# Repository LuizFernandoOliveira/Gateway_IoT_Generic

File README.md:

# Gateway IoT Multi-Protocolo (MSP430 version)

## Descrição
Diferentemente das tradicionais SBCs baseadas em MPUs de alta performance, este circuito de Gateway IoT é baseado em um MCU para aplicações que necessitam gerenciar a sua rede IoT no modo ultra-low power.

---

## Descrições técnicas
- Microcontrolador: MSP430FR6005;
- Alimentação externa de 5V;
- Possui a capacidade de realizar a comunicação com até 4 periféricos UARTs padrão FAPLO;
- Capacidade de se comunicar por meio do protocolo de comunicação:
  - 4 x UARTs (UART0, UART1, UART2, UART3);
  - 1 x RS-485 (UART2);
  - 1 x I2C (UART1);
  - 2 x SPIs (UART0 e UART1);
- Possui LEDs de troca de dados da UART0;
- Todos os demais pinos dos conectores padrão FAPLO podem ser usados como pinos de propósito gerais.

---

## Estrutura do repositório
Os arquivos de hardware foram desenvolvidos utilizando o KiCad 9.0.
- **`.kicad_pcb`**: Layout da placa de circuito impresso (Board).
- **`.kicad_sch`**: Esquemático eletrônico do sistema (Schematic).
- **`.kicad_pro`**: Gerenciador de projeto do KiCad (Project).

---

## Autor
**Dr. Luiz Fernando Pinto de Oliveira**

*Engenheiro Eletrônico especializado em Sistemas Embarcados e Ultra-Low Power.*
- **Website:** [FAPLO](https://faplo.webnode.page/)
- **LinkedIn:** [lfpo](https://www.linkedin.com/in/lfpo/)

---

Shield: [![CC BY-NC-ND 4.0][cc-by-nc-nd-shield]][cc-by-nc-nd]

This work is licensed under a
[Creative Commons Attribution-NonCommercial-NoDerivs 4.0 International License][cc-by-nc-nd].

[![CC BY-NC-ND 4.0][cc-by-nc-nd-image]][cc-by-nc-nd]

[cc-by-nc-nd]: http://creativecommons.org/licenses/by-nc-nd/4.0/
[cc-by-nc-nd-image]: https://licensebuttons.net/l/by-nc-nd/4.0/88x31.png
[cc-by-nc-nd-shield]: https://img.shields.io/badge/License-CC%20BY--NC--ND%204.0-lightgrey.svg

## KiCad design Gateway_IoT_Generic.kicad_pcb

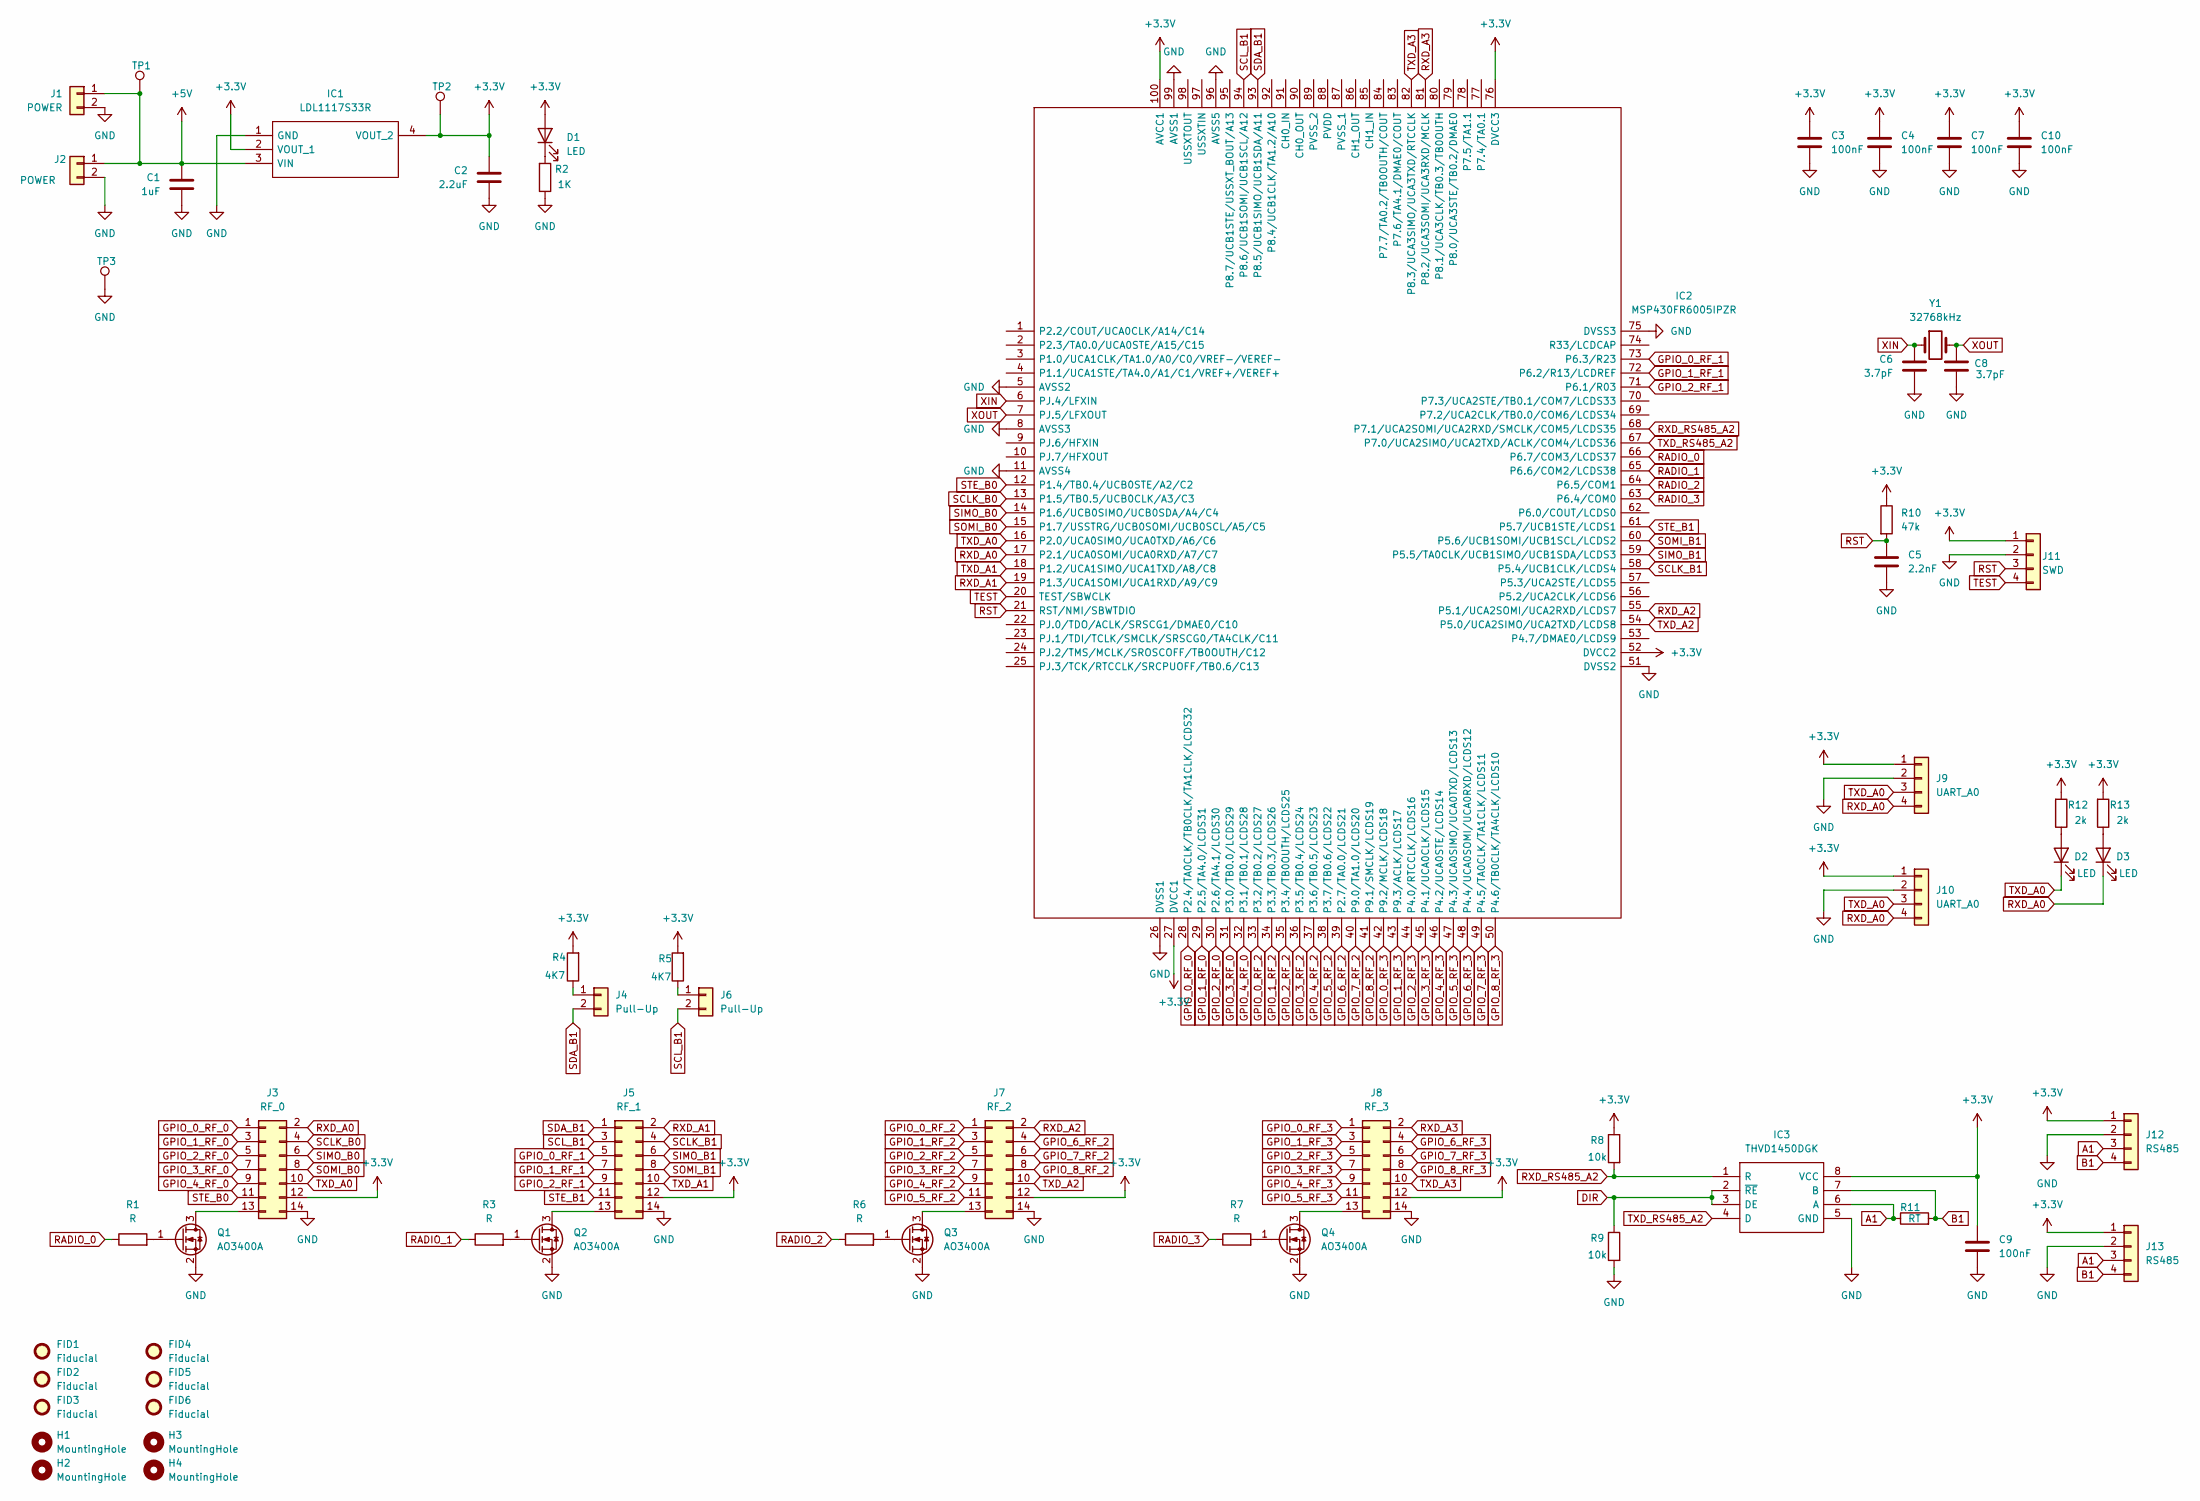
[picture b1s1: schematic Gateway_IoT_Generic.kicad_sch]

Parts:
C1: 1uF; C_0805_2012Metric
C2: 2.2uF; C_0805_2012Metric
C3, C4, C7, C9, C10: 100nF; C_0805_2012Metric
C5: 2.2nF; C_0805_2012Metric
C6, C8: 3.7pF; C_0805_2012Metric
D1, D2, D3: LED; LED_0805_2012Metric
FID1, FID2, FID3, FID4, FID5, FID6: Fiducial; Fiducial_1mm_Mask2mm
H1, H2, H3, H4: MountingHole; MountingHole_3.2mm_M3_DIN965
IC1: LDL1117S33R; SOT230P700X180-4N; Manufacturer_Part_Number LDL1117S33R; Mouser Part Number 511-LDL1117S33R
IC2: MSP430FR6005IPZR; QFP50P1600X1600X160-100N; Manufacturer_Part_Number MSP430FR6005IPZR; Mouser Part Number 595-MSP430FR6005IPZR
IC3: THVD1450DGK; SOP65P490X110-8N; Manufacturer_Part_Number THVD1450DGK; Mouser Part Number 595-THVD1450DGK
J1: POWER; PinHeader_1x02_P2.54mm_Vertical
J2: POWER; BarrelJack_Horizontal
J3: RF_0; PinHeader_2x07_P2.54mm_Vertical
J4, J6: Pull-Up; PinHeader_1x02_P2.54mm_Vertical
J5: RF_1; PinHeader_2x07_P2.54mm_Vertical
J7: RF_2; PinHeader_2x07_P2.54mm_Vertical
J8: RF_3; PinHeader_2x07_P2.54mm_Vertical
J9: UART_A0; PinHeader_1x04_P2.54mm_Vertical
J10: UART_A0; JST_XH_S4B-XH-A_1x04_P2.50mm_Horizontal
J11: SWD; PinHeader_1x04_P1.27mm_Vertical
J12: RS485; PinHeader_1x04_P2.54mm_Vertical
J13: RS485; PhoenixContact_MSTBA_2,5_4-G-5,08_1x04_P5.08mm_Horizontal
Q1, Q2, Q3, Q4: AO3400A; SOT-23
R1, R3, R6, R7: R; R_0805_2012Metric
R2: 1K; R_0805_2012Metric
R4, R5: 4K7; R_0805_2012Metric
R8, R9: 10k; R_0805_2012Metric
R10: 47k; R_0805_2012Metric
R11: RT; R_1206_3216Metric
R12, R13: 2k; R_0805_2012Metric
TP1, TP2, TP3: TestPoint; TestPoint_Loop_D1.80mm_Drill1.0mm_Beaded
Y1: 32768kHz; D_0805_2012Metric

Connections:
+3.3V: C2.1, C3.1, C4.1, C7.1, C9.1, C10.1, D1.2 (A), IC1.2 (VOUT_1), IC1.4 (VOUT_2), IC2.27 (DVCC1), IC2.52 (DVCC2), IC2.76 (DVCC3), IC2.100 (AVCC1), IC3.8 (VCC), J3.12, J5.12, J7.12, J8.12, J9.1, J10.1, J11.1, J12.1, J13.1, R4.2, R5.2, R8.1, R10.1, R12.2, R13.2, TP2.1
+5V: C1.1, IC1.3 (VIN), J1.1, J2.1, TP1.1
A1: IC3.6 (A), J12.3, J13.3, R11.1
B1: IC3.7 (B), J12.4, J13.4, R11.2
DIR: IC3.2 (~RE), IC3.3 (DE), R9.1
GND: C1.2, C2.2, C3.2, C4.2, C5.2, C6.2, C7.2, C8.2, C9.2, C10.2, IC1.1 (GND), IC2.5 (AVSS2), IC2.8 (AVSS3), IC2.11 (AVSS4), IC2.26 (DVSS1), IC2.51 (DVSS2), IC2.75 (DVSS3), IC2.96 (AVSS5), IC2.99 (AVSS1), IC3.5 (GND), J1.2, J2.2, J3.14, J5.14, J7.14, J8.14, J9.2, J10.2, J11.2, J12.2, J13.2, Q1.2 (S), Q2.2 (S), Q3.2 (S), Q4.2 (S), R2.1, R9.2, TP3.1
GPIO_0_RF_0: IC2.28 (P2.4/TA0CLK/TB0CLK/TA1CLK/LCDS32), J3.1
GPIO_0_RF_1: IC2.73 (P6.3/R23), J5.5
GPIO_0_RF_2: IC2.33 (P3.2/TB0.2/LCDS27), J7.1
GPIO_0_RF_3: IC2.42 (P9.2/MCLK/LCDS18), J8.1
GPIO_1_RF_0: IC2.29 (P2.5/TA4.0/LCDS31), J3.3
GPIO_1_RF_1: IC2.72 (P6.2/R13/LCDREF), J5.7
GPIO_1_RF_2: IC2.34 (P3.3/TB0.3/LCDS26), J7.3
GPIO_1_RF_3: IC2.43 (P9.3/ACLK/LCDS17), J8.3
GPIO_2_RF_0: IC2.30 (P2.6/TA4.1/LCDS30), J3.5
GPIO_2_RF_1: IC2.71 (P6.1/R03), J5.9
GPIO_2_RF_2: IC2.35 (P3.4/TB0OUTH/LCDS25), J7.5
GPIO_2_RF_3: IC2.44 (P4.0/RTCCLK/LCDS16), J8.5
GPIO_3_RF_0: IC2.31 (P3.0/TB0.0/LCDS29), J3.7
GPIO_3_RF_2: IC2.36 (P3.5/TB0.4/LCDS24), J7.7
GPIO_3_RF_3: IC2.45 (P4.1/UCA0CLK/LCDS15), J8.7
GPIO_4_RF_0: IC2.32 (P3.1/TB0.1/LCDS28), J3.9
GPIO_4_RF_2: IC2.37 (P3.6/TB0.5/LCDS23), J7.9
GPIO_4_RF_3: IC2.46 (P4.2/UCA0STE/LCDS14), J8.9
GPIO_5_RF_2: IC2.38 (P3.7/TB0.6/LCDS22), J7.11
GPIO_5_RF_3: IC2.47 (P4.3/UCA0SIMO/UCA0TXD/LCDS13), J8.11
GPIO_6_RF_2: IC2.39 (P2.7/TA0.0/LCDS21), J7.4
GPIO_6_RF_3: IC2.48 (P4.4/UCA0SOMI/UCA0RXD/LCDS12), J8.4
GPIO_7_RF_2: IC2.40 (P9.0/TA1.0/LCDS20), J7.6
GPIO_7_RF_3: IC2.49 (P4.5/TA0CLK/TA1CLK/LCDS11), J8.6
GPIO_8_RF_2: IC2.41 (P9.1/SMCLK/LCDS19), J7.8
GPIO_8_RF_3: IC2.50 (P4.6/TB0CLK/TA4CLK/LCDS10), J8.8
unnamed: D1.1 (K), R2.2
unnamed: D2.2 (A), R12.1
unnamed: D3.2 (A), R13.1
unnamed: J3.13, Q1.3 (D)
unnamed: J4.1, R4.1
unnamed: J5.13, Q2.3 (D)
unnamed: J6.1, R5.1
unnamed: J7.13, Q3.3 (D)
unnamed: J8.13, Q4.3 (D)
unnamed: Q1.1 (G), R1.2
unnamed: Q2.1 (G), R3.2
unnamed: Q3.1 (G), R6.2
unnamed: Q4.1 (G), R7.2
RADIO_0: IC2.66 (P6.7/COM3/LCDS37), R1.1
RADIO_1: IC2.65 (P6.6/COM2/LCDS38), R3.1
RADIO_2: IC2.64 (P6.5/COM1), R6.1
RADIO_3: IC2.63 (P6.4/COM0), R7.1
RST: C5.1, IC2.21 (RST/NMI/SBWTDIO), J11.3, R10.2
RXD_A0: D3.1 (K), IC2.17 (P2.1/UCA0SOMI/UCA0RXD/A7/C7), J3.2, J9.4, J10.4
RXD_A1: IC2.19 (P1.3/UCA1SOMI/UCA1RXD/A9/C9), J5.2
RXD_A2: IC2.55 (P5.1/UCA2SOMI/UCA2RXD/LCDS7), J7.2
RXD_A3: IC2.81 (P8.2/UCA3SOMI/UCA3RXD/MCLK), J8.2
RXD_RS485_A2: IC2.68 (P7.1/UCA2SOMI/UCA2RXD/SMCLK/COM5/LCDS35), IC3.1 (R), R8.2
SCLK_B0: IC2.13 (P1.5/TB0.5/UCB0CLK/A3/C3), J3.4
SCLK_B1: IC2.58 (P5.4/UCB1CLK/LCDS4), J5.4
SCL_B1: IC2.94 (P8.6/UCB1SOMI/UCB1SCL/A12), J5.3, J6.2
SDA_B1: IC2.93 (P8.5/UCB1SIMO/UCB1SDA/A11), J4.2, J5.1
SIMO_B0: IC2.14 (P1.6/UCB0SIMO/UCB0SDA/A4/C4), J3.6
SIMO_B1: IC2.59 (P5.5/TA0CLK/UCB1SIMO/UCB1SDA/LCDS3), J5.6
SOMI_B0: IC2.15 (P1.7/USSTRG/UCB0SOMI/UCB0SCL/A5/C5), J3.8
SOMI_B1: IC2.60 (P5.6/UCB1SOMI/UCB1SCL/LCDS2), J5.8
STE_B0: IC2.12 (P1.4/TB0.4/UCB0STE/A2/C2), J3.11
STE_B1: IC2.61 (P5.7/UCB1STE/LCDS1), J5.11
TEST: IC2.20 (TEST/SBWCLK), J11.4
TXD_A0: D2.1 (K), IC2.16 (P2.0/UCA0SIMO/UCA0TXD/A6/C6), J3.10, J9.3, J10.3
TXD_A1: IC2.18 (P1.2/UCA1SIMO/UCA1TXD/A8/C8), J5.10
TXD_A2: IC2.54 (P5.0/UCA2SIMO/UCA2TXD/LCDS8), J7.10
TXD_A3: IC2.82 (P8.3/UCA3SIMO/UCA3TXD/RTCCLK), J8.10
TXD_RS485_A2: IC2.67 (P7.0/UCA2SIMO/UCA2TXD/ACLK/COM4/LCDS36), IC3.4 (D)
XIN: C6.1, IC2.6 (PJ.4/LFXIN), Y1.1
XOUT: C8.1, IC2.7 (PJ.5/LFXOUT), Y1.2

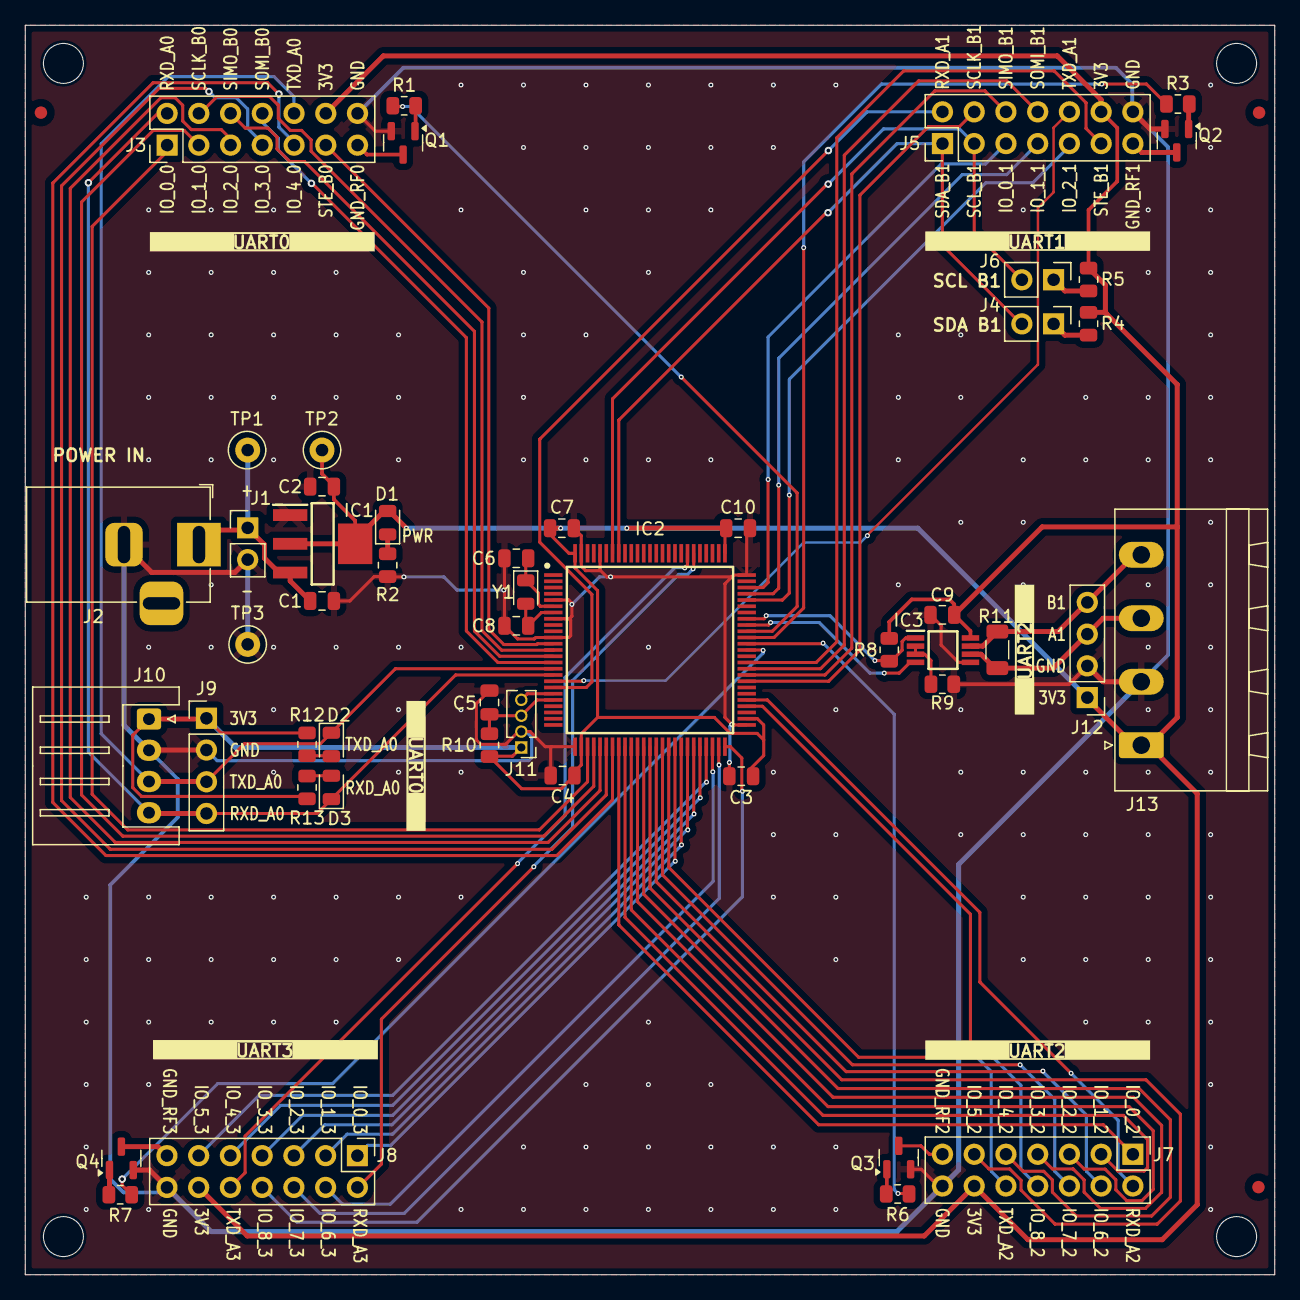
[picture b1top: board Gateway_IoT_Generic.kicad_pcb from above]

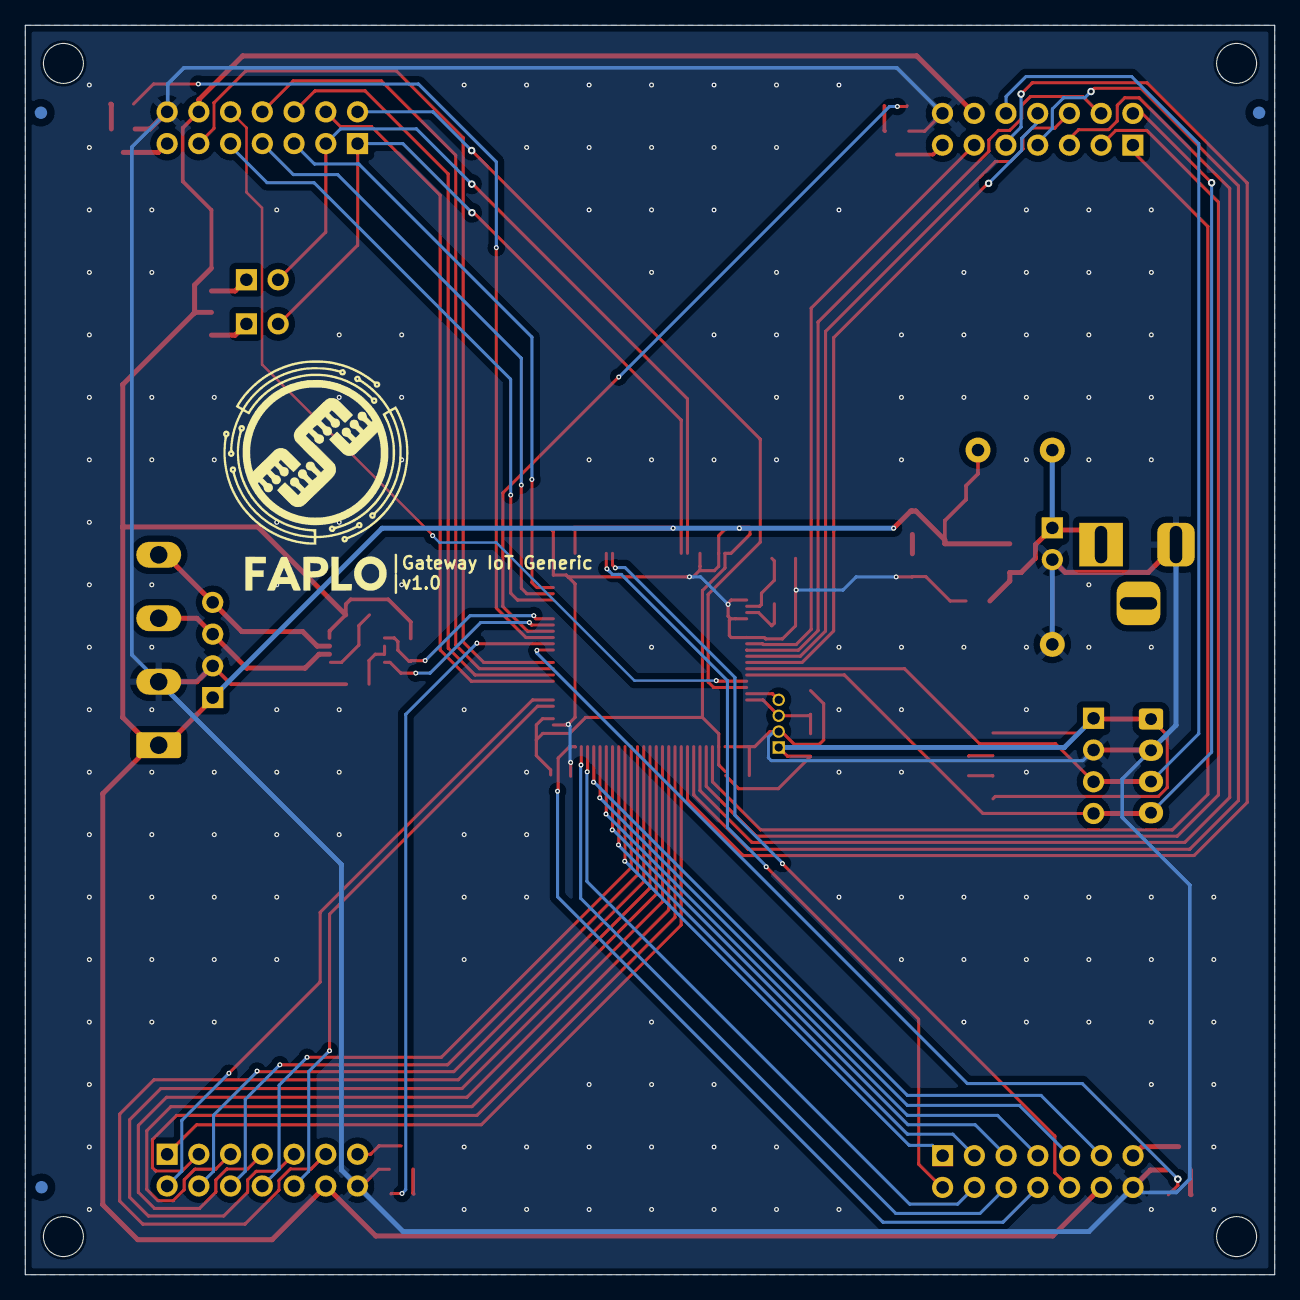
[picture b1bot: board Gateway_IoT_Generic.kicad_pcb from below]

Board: 2 copper layers, 100.0 x 100.0 mm, 60 parts (3 on the bottom side), 73 nets.

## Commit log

2026-04-17 Commit inicial
2026-04-17 Revise README with project details and specifications
    Updated project title and added detailed project description, specifications, repository structure, usage instructions, system architecture, author information, and license details.
2026-04-17 Revise README for MSP430 version and update details
    Updated project description and specifications for MSP430 version. Changed hardware details and author information.
2026-04-17 Add Creative Commons license
    Added the Creative Commons Attribution-NonCommercial-NoDerivatives 4.0 International Public License to the project.
